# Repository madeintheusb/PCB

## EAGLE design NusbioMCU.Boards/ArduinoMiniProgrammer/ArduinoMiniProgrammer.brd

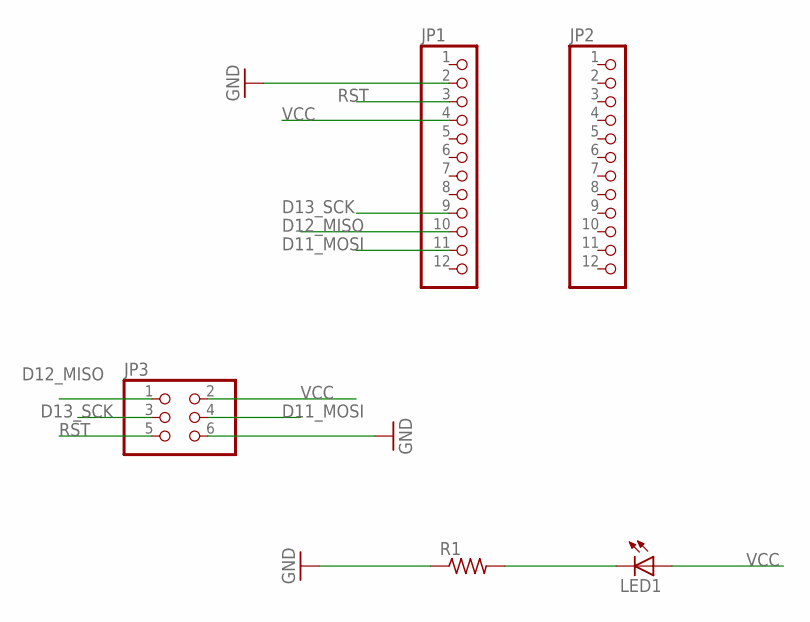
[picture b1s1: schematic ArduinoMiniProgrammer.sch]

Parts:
JP1, JP2: PINHD-1X12; 1X12
JP3: PINHD-2X3; 2X03
LED1: LEDCHIPLED_0805; CHIPLED_0805
R1: R-US_R0805; R0805

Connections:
A0_SECURITY: LED1.C, R1.2
D11_MOSI: JP1.11, JP3.4
D12_MISO: JP1.10, JP3.1
D13_SCK: JP1.9, JP3.3
GND: JP1.2, JP3.6, R1.1
RST: JP1.3, JP3.5
VCC: JP1.4, JP3.2, LED1.A

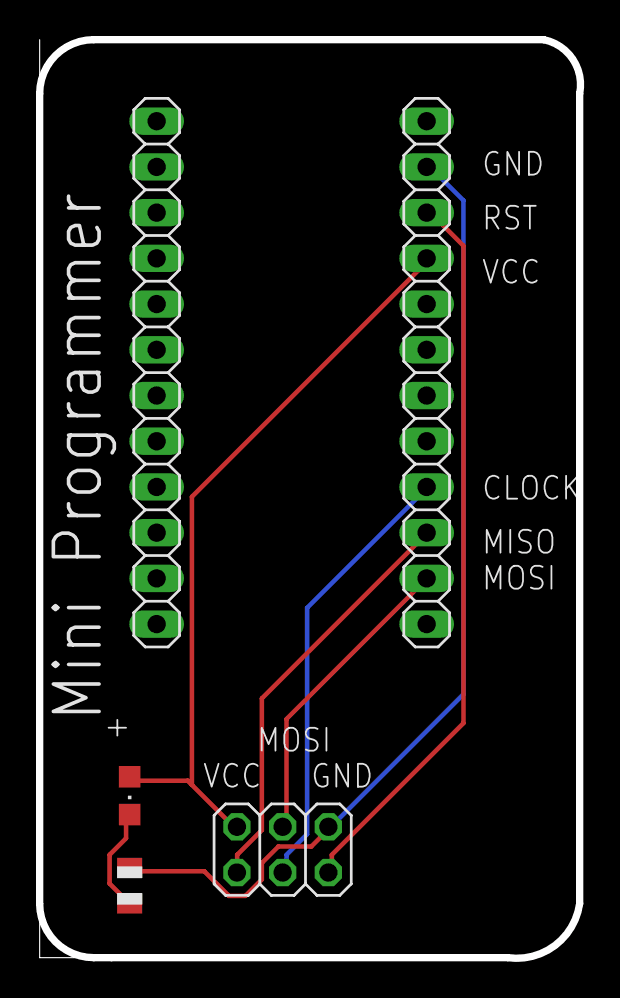
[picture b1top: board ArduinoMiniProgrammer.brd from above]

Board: 2 copper layers, 30.0 x 51.0 mm, 5 parts (0 on the bottom side), 7 nets.

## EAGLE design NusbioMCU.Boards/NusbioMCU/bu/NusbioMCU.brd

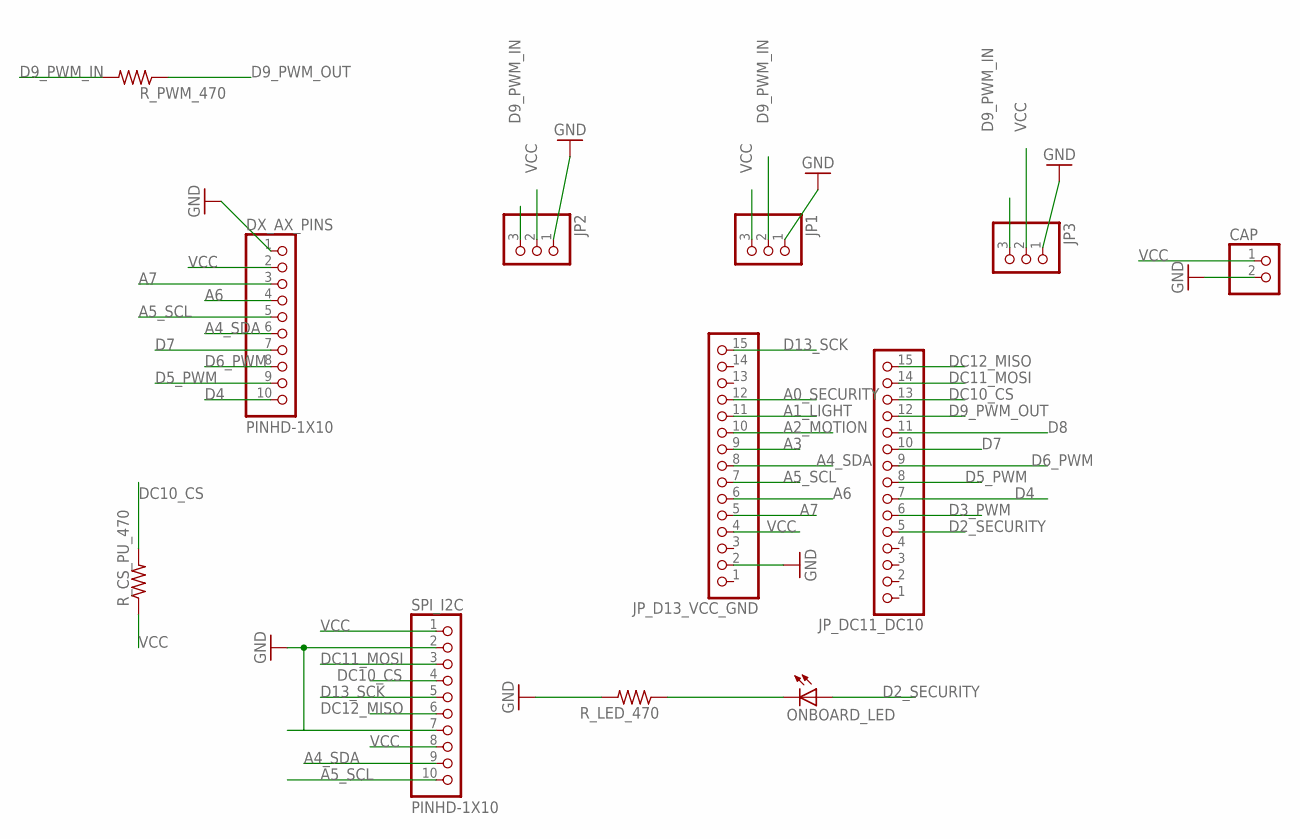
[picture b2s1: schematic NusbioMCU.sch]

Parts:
CAP: PINHD-1X2; 1X02
DX_AX_PINS: PINHD-1X10; 1X10-BIG
JP1, JP2, JP3: PINHD-1X3; 1X03
JP_D13_VCC_GND: PINHD-1X15; 1X15
JP_DC11_DC10: PINHD-1X15; 1X15
ONBOARD_LED: LEDSMT1206; 1206
R_CS_PU_470: R-US_R1206; R1206
R_LED_470: R-US_R1206; R1206
R_PWM_470: R-US_R1206; R1206
SPI_I2C: PINHD-1X10; 1X10-BIG

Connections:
A0_SECURITY: JP_D13_VCC_GND.12
A1_LIGHT: JP_D13_VCC_GND.11
A2_MOTION: JP_D13_VCC_GND.10
A3: JP_D13_VCC_GND.9
A4_SDA: DX_AX_PINS.6, JP_D13_VCC_GND.8, SPI_I2C.9
A5_SCL: DX_AX_PINS.5, JP_D13_VCC_GND.7, SPI_I2C.10
A6: DX_AX_PINS.4, JP_D13_VCC_GND.6
A7: DX_AX_PINS.3, JP_D13_VCC_GND.5
D2_SECURITY: JP_DC11_DC10.5, ONBOARD_LED.A
D3_PWM: JP_DC11_DC10.6
D4: DX_AX_PINS.10, JP_DC11_DC10.7
D5_PWM: DX_AX_PINS.9, JP_DC11_DC10.8
D6_PWM: DX_AX_PINS.8, JP_DC11_DC10.9
D7: DX_AX_PINS.7, JP_DC11_DC10.10
D8: JP_DC11_DC10.11
D9_PWM_IN: JP1.2, JP2.3, JP3.3, R_PWM_470.2
D9_PWM_OUT: JP_DC11_DC10.12, R_PWM_470.1
D13_SCK: JP_D13_VCC_GND.15, SPI_I2C.5
DC10_CS: JP_DC11_DC10.13, R_CS_PU_470.2, SPI_I2C.4
DC11_MOSI: JP_DC11_DC10.14, SPI_I2C.3
DC12_MISO: JP_DC11_DC10.15, SPI_I2C.6
GND: CAP.2, DX_AX_PINS.1, JP1.1, JP2.1, JP3.1, JP_D13_VCC_GND.2, R_LED_470.2, SPI_I2C.2, SPI_I2C.7
unnamed: ONBOARD_LED.C, R_LED_470.1
VCC: CAP.1, DX_AX_PINS.2, JP1.3, JP2.2, JP3.2, JP_D13_VCC_GND.4, R_CS_PU_470.1, SPI_I2C.1, SPI_I2C.8

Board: 2 copper layers, 12 parts (0 on the bottom side), 18 nets, no tracks yet.

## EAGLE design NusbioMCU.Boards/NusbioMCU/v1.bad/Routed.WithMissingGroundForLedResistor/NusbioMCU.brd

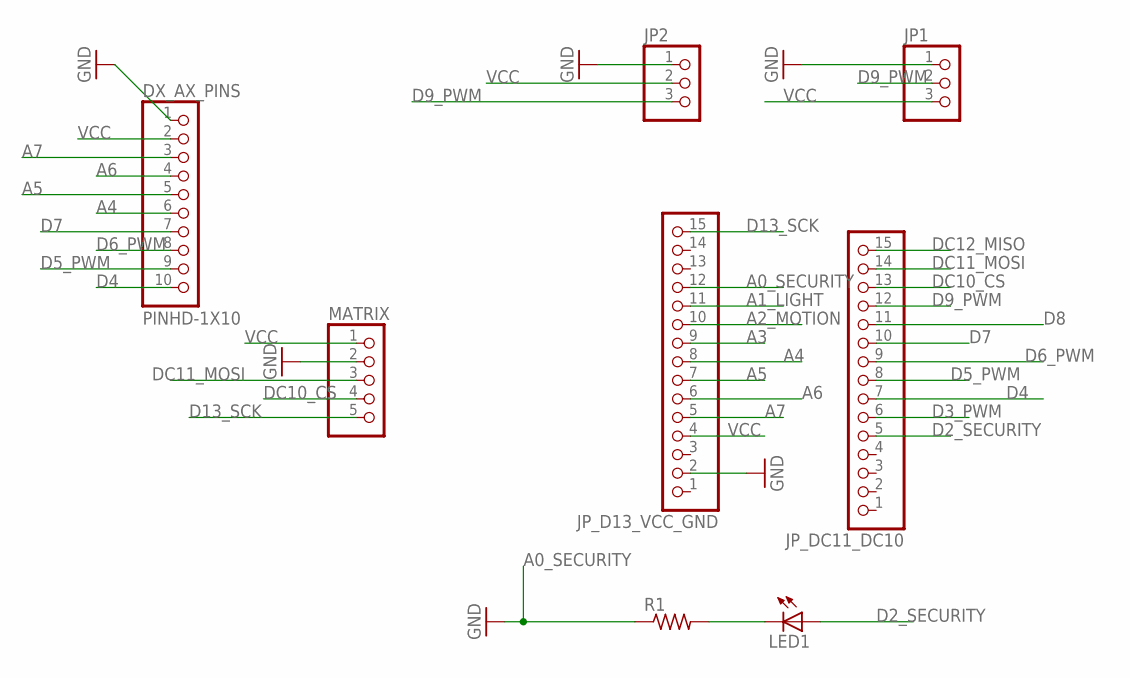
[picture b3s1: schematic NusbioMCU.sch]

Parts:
DX_AX_PINS: PINHD-1X10; 1X10-BIG
JP1, JP2: PINHD-1X3; 1X03
JP_D13_VCC_GND: PINHD-1X15; 1X15
JP_DC11_DC10: PINHD-1X15; 1X15
LED1: LEDCHIPLED_0805; CHIPLED_0805
MATRIX: PINHD-1X5; 1X05
R1: R-US_R0805; R0805

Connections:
A0_SECURITY: JP_D13_VCC_GND.12, R1.1
A1_LIGHT: JP_D13_VCC_GND.11
A2_MOTION: JP_D13_VCC_GND.10
A3: JP_D13_VCC_GND.9
A4: DX_AX_PINS.6, JP_D13_VCC_GND.8
A5: DX_AX_PINS.5, JP_D13_VCC_GND.7
A6: DX_AX_PINS.4, JP_D13_VCC_GND.6
A7: DX_AX_PINS.3, JP_D13_VCC_GND.5
D2_SECURITY: JP_DC11_DC10.5, LED1.A
D3_PWM: JP_DC11_DC10.6
D4: DX_AX_PINS.10, JP_DC11_DC10.7
D5_PWM: DX_AX_PINS.9, JP_DC11_DC10.8
D6_PWM: DX_AX_PINS.8, JP_DC11_DC10.9
D7: DX_AX_PINS.7, JP_DC11_DC10.10
D8: JP_DC11_DC10.11
D9_PWM: JP1.2, JP2.3, JP_DC11_DC10.12
D13_SCK: JP_D13_VCC_GND.15, MATRIX.5
DC10_CS: JP_DC11_DC10.13, MATRIX.4
DC11_MOSI: JP_DC11_DC10.14, MATRIX.3
DC12_MISO: JP_DC11_DC10.15
GND: DX_AX_PINS.1, JP1.1, JP2.1, JP_D13_VCC_GND.2, MATRIX.2
unnamed: LED1.C, R1.2
VCC: DX_AX_PINS.2, JP1.3, JP2.2, JP_D13_VCC_GND.4, MATRIX.1

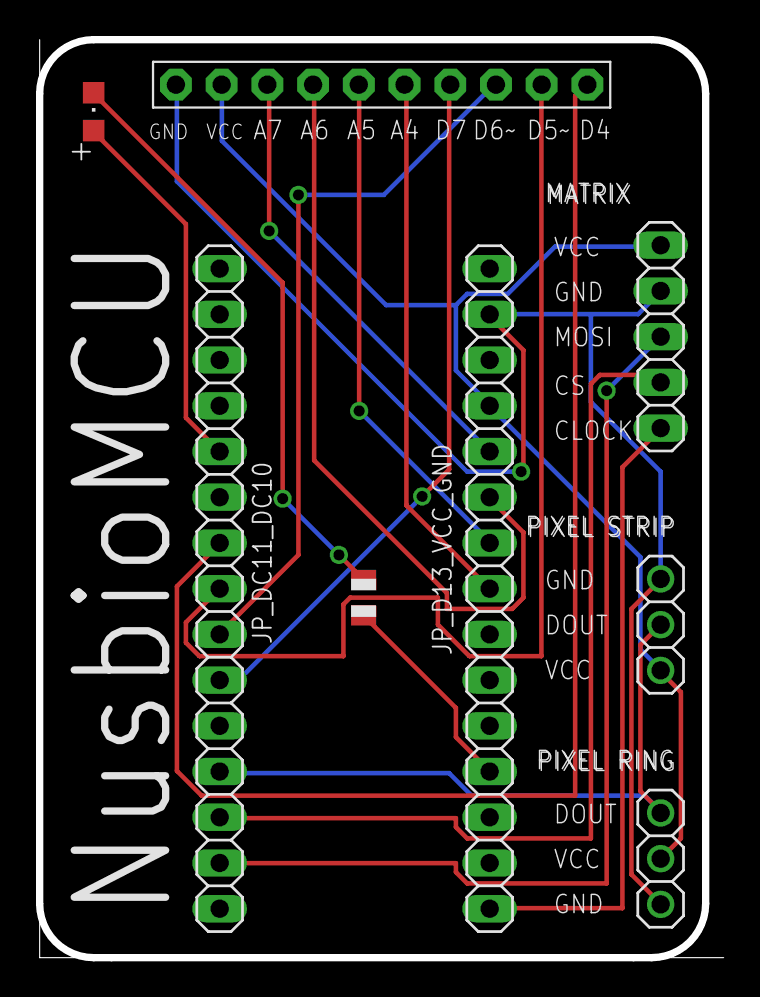
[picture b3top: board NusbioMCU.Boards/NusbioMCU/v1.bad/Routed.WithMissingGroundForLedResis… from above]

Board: 2 copper layers, 38.0 x 51.0 mm, 8 parts (0 on the bottom side), 17 nets.
